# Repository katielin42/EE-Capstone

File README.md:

# EE-Capstone
This repository is the master collection of technical files (excluding reports and posters) for ECE490/491 group 1 capstone - Formula SAE EVCU (electric vehicle control unit) project. Group members are enrolled in electrical engineering at the U of A. Our valuable consultant and helpers are staff and instructors of ECE 490/491 as well as Le Minh Dang, a computer engineering student, all of whom are from the University of Alberta as well. 

## Hardware
Below is a high level hardware block diagram describing our fabricated PCB. Detailed 3d-view of the PCB and schematic can be found under Hardware Design/EVCU Rev B/EVCU. 

Design created by: Thomas Osei-Bonsu Jr. and Katie Lin

## Software
Below is a high level software flowchart block diagram describing our software control flow. Detailed Documentation about code can be found below. We are using STM32Cube IDE to develop our code currently, so our configuration for our software has mostly been STM32Cube IDE presets.

Design created by: Katie Lin and Thomas Osei-Bonsu Jr.

**Libraries/modules/middlewares we used:** 

+ **FreeRTOS**: for scheduling tasks and other parallel programming functionalities

+ **FATFS**: for communications and r/w functions with the SD card

**Current code structure**:

```STM32_test.ioc```: Settings file for pin configurations, turning peripherials on/off with STM32Cube IDE...etc.

```main.c```: pin defines, generation of global tasks/mutexes/threads and starting the kernel. Also imports all the other functions and runs them. 

```SD_task.c && SD_task.h```: calls functions to perform r/w functions to and from sd card, as well as mount/dismount...etc. 

```ADC_task.c && ADC_task.h```: processes values going into ADC pins and saves them in an intermediate buffer for further logic/processing. 

```CAN_task.c && CAN_task.h```: processes operations relevant to STM32 BxCAN functionalities, such as sending and receiving CAN messages, encoding and decoding of such messages...etc. 

```controller_task.c && controller_task.h```: a giant state machine with cases, interrupts...etc that links all the tasks together. Based on the inputs and outputs of the task files described above, decide the next steps of what the MCU needs to do, usually sending CAN messages and error logging upon error detection. 

## User Manual (for EVCU PCB)

Above is a physical image of the EVCU PCB. 

**Hardware Setup**

The setup for EVCU PCB should be done after reviewing the schematic and layout, which can be found under Hardware Design/EVCU Rev B/EVCU. For the EVCU PCB, provide a 12v DC input at J2 and ground signal. 

At J3, the APPS VPA/VPA2 and BSE sensor signal inputs to the ADC are labelled. Please consult the accelerator pedal datasheets to hook the APPS pedal/BSE sensors up correctly. 

The J5 DB9 connector is the CAN connector that can be hooked up to the motor controller. Our CAN bus speed is 0.5Mbit/second, so configure the motor controller accordingly. 

Before powering the board up, please ensure a microSD card is inserted and the sensors are powered and operational and connected to the analog inputs of this PCB. The current firmware will start running once the board is powered up. If any firmware errors occur, disconnect the PCB from power, ensure the hardware components are all connected, and reconnect the PCB to power. 

**Firmware Setup**

If one wishes to modify the firmware, please download STM32CubeIDE and clone this repository. The firmware project name in this repository is STM32_Test. Then, hook up serial wire debug pins in J1 to a debug programmer. These configurations can be found online. Then, clicking on the run or debug button will flash the updated code onto the EVCU PCB MCU. 

+ If the error conditions for the analog APPS/BSE sensors need to be modified, they can be changed in controller_task.c under the function check_error_condition(). Currently the code checks for APPS/BSE <0.5 or >4.5V as specified by the rules, but I believe the datasheet for one of the sensors says otherwise. 
+ If any CAN address/settings need to be modified, they can be changed in CAN_task.c

**Caveats**
+ If SD card logs aren't removed after powering off the board, they will be wiped at the next instance the board is powered up. 
+ SD card cannot be removed in the middle of operation. 
+ SD card might die due to too many writes, just replace a new micro SD card if you notice the EVCU firmware behaving weirdly with the SD card. 

**The code also works with the dev board. However, several changes need to be made in the .ioc**
+ uSD_detect pin needs to be changed from PC7 to PA5. 
+ Clock configurations need to be set: HSE from BYPASS to crystal/ceramic oscillator, and disable LSE. 
+ Connect the CAN transciever module to the dev board via the USB breakout board, connect to the non ST-Link microUSB input on the dev board (there are only two). 

Finally, save those changes to the .ioc file, close it, and flash the code onto the dev board.

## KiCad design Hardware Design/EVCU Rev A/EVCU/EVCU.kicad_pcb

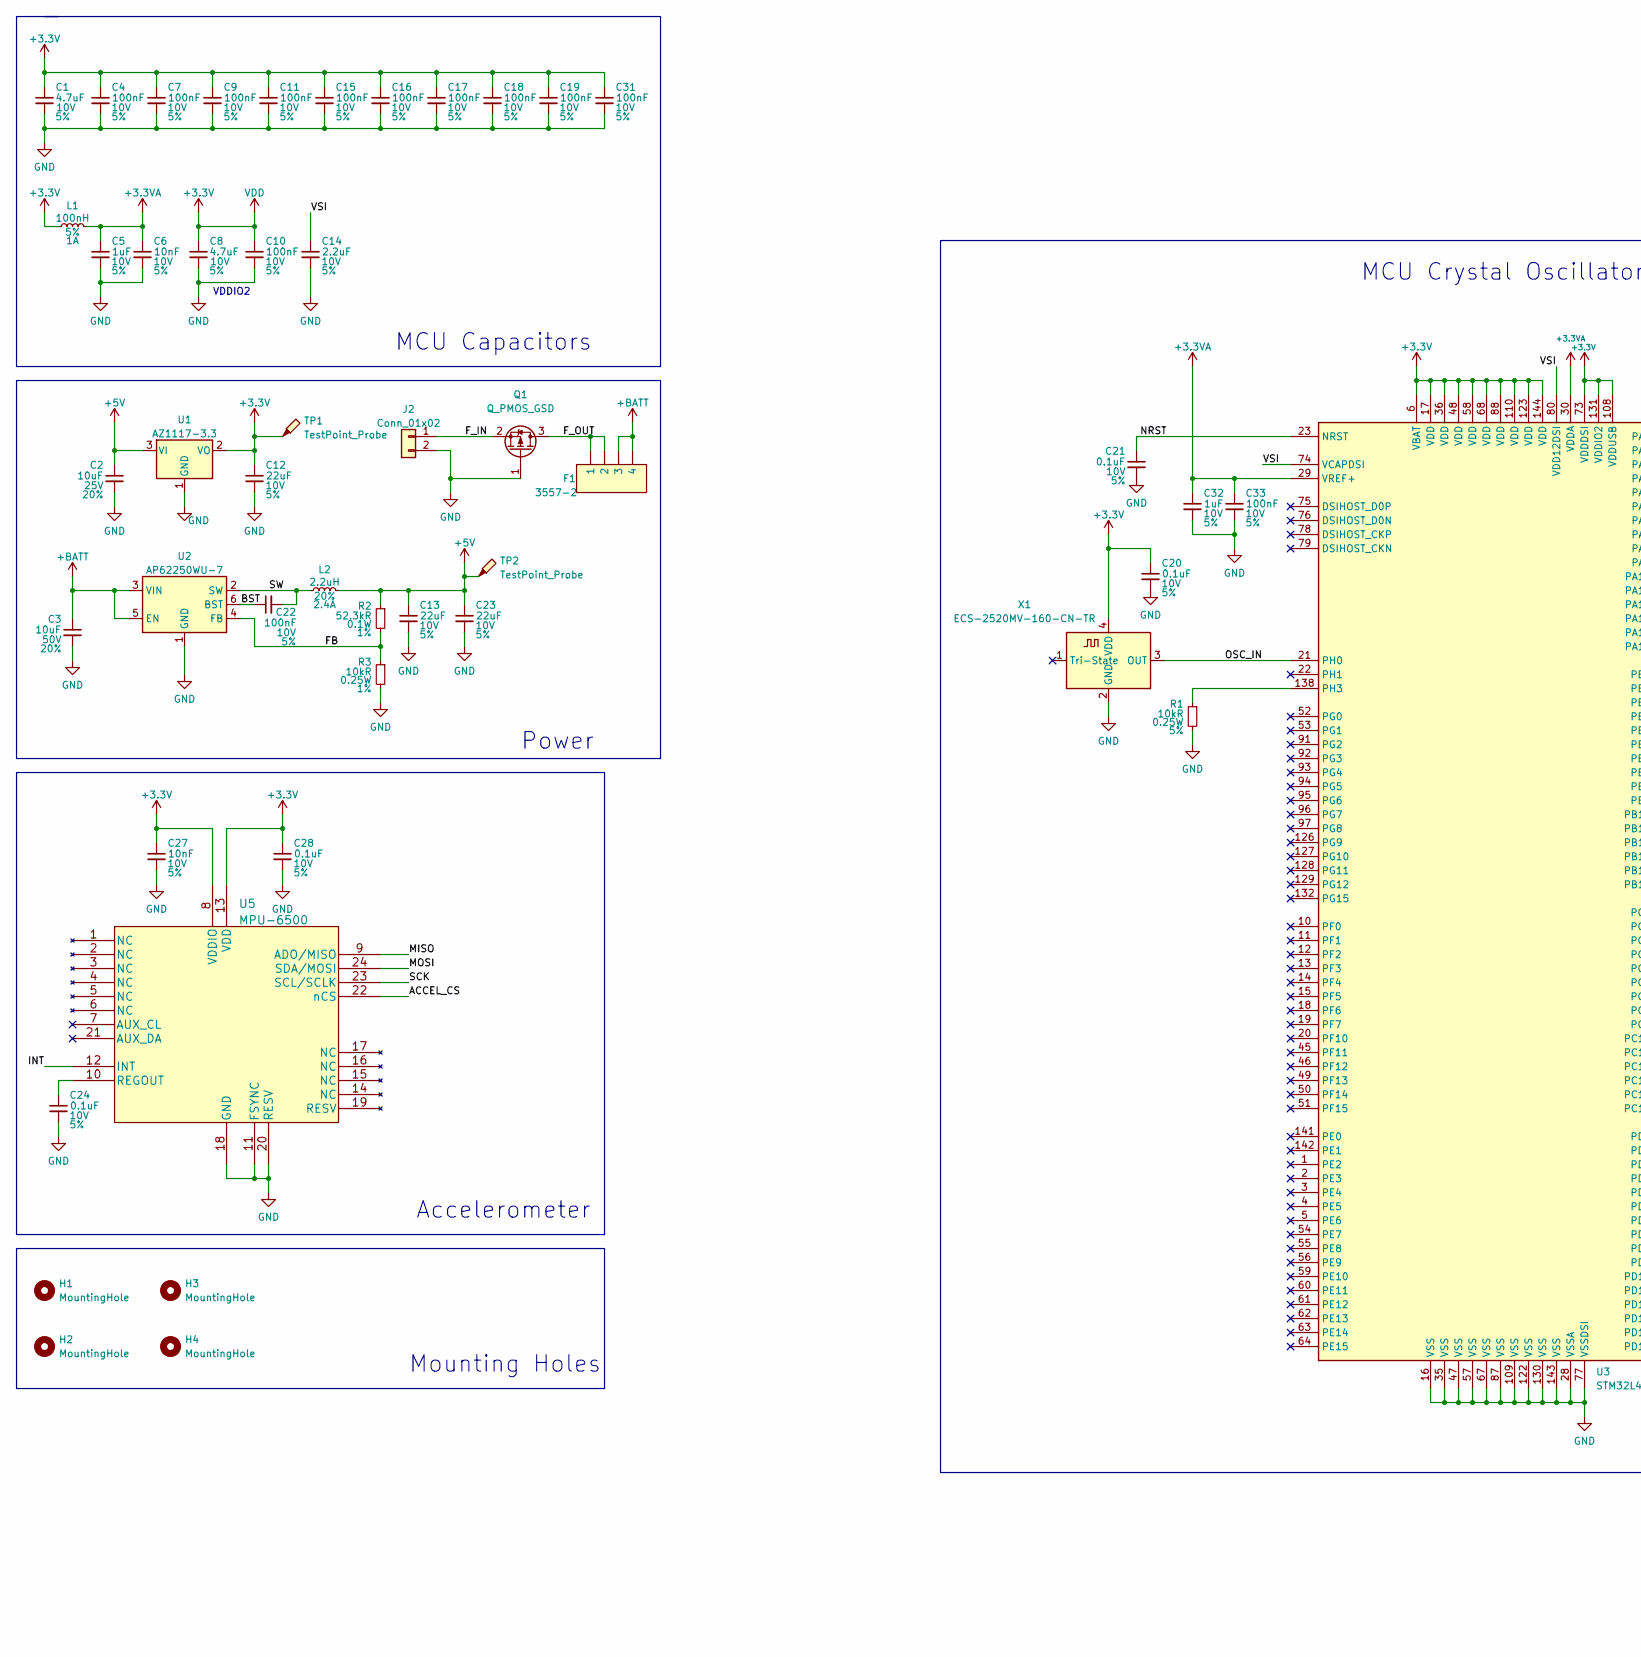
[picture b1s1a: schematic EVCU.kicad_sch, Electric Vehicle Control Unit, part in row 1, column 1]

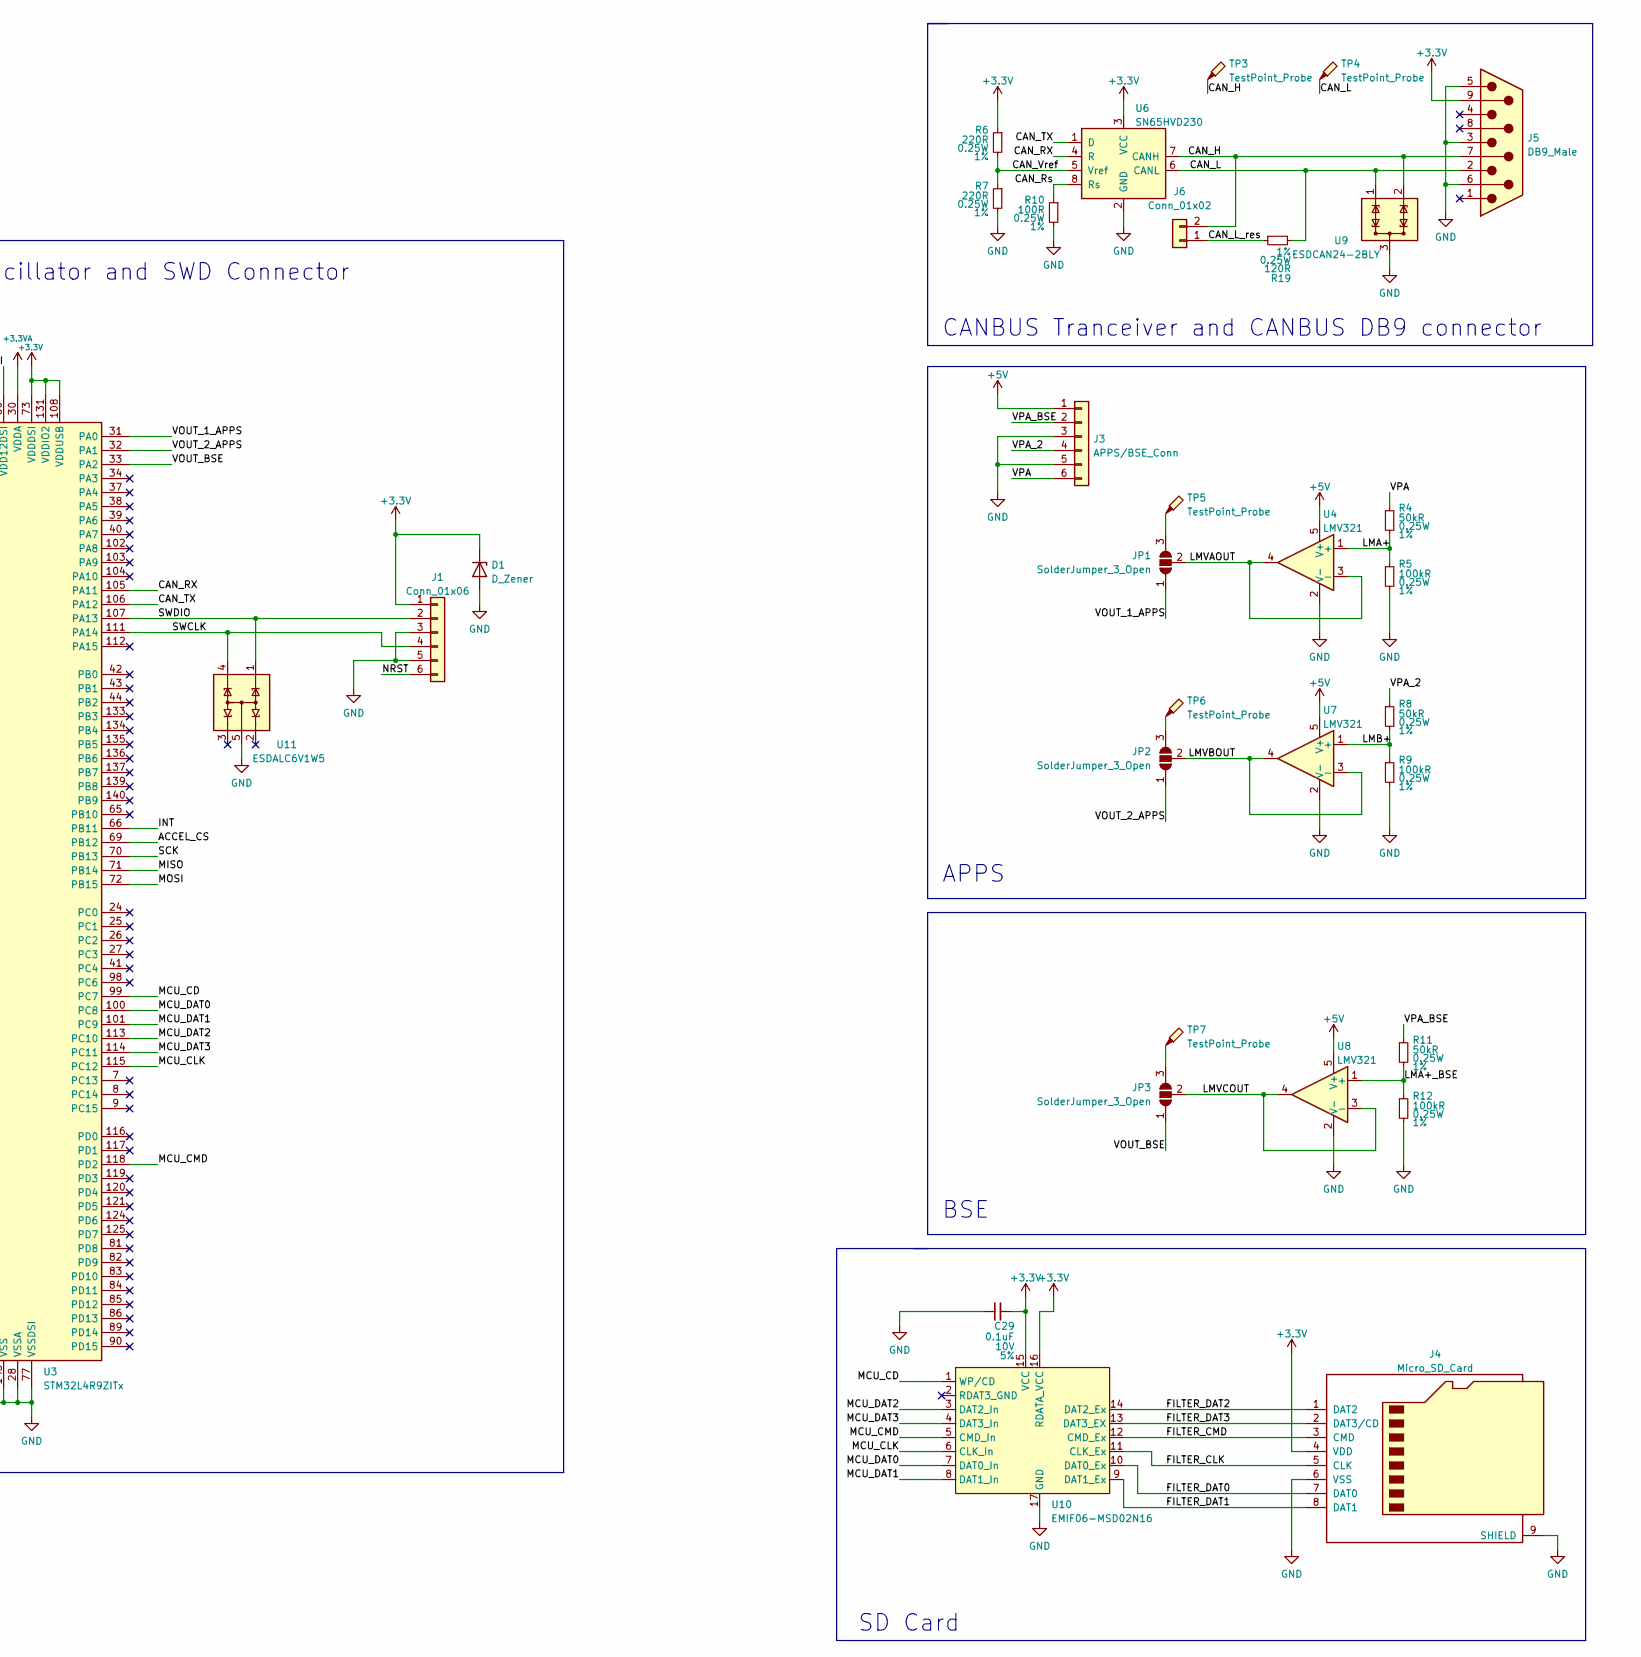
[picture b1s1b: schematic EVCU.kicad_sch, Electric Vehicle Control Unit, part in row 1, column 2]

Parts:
C1, C8: 4.7uF; C_0603_1608Metric_Pad1.08x0.95mm_HandSolder; Tolerance 5%; Rating 10V
C2: 10uF; C_0603_1608Metric_Pad1.08x0.95mm_HandSolder; Rating 25V; Tolerance 20%
C3: 10uF; C_1206_3216Metric_Pad1.33x1.80mm_HandSolder; Rating 50V; Tolerance 20%
C4, C7, C9, C10, C11, C15, C16, C17, C18, C19, C22, C31, C33: 100nF; C_0603_1608Metric_Pad1.08x0.95mm_HandSolder; Rating 10V; Tolerance 5%
C5, C32: 1uF; C_0603_1608Metric_Pad1.08x0.95mm_HandSolder; Rating 10V; Tolerance 5%
C6, C27: 10nF; C_0603_1608Metric_Pad1.08x0.95mm_HandSolder; Rating 10V; Tolerance 5%
C12, C13, C23: 22uF; C_0603_1608Metric_Pad1.08x0.95mm_HandSolder; Rating 10V; Tolerance 5%
C14: 2.2uF; C_0603_1608Metric_Pad1.08x0.95mm_HandSolder; Rating 10V; Tolerance 5%
C20, C21, C24, C28, C29: 0.1uF; C_0603_1608Metric_Pad1.08x0.95mm_HandSolder; Rating 10V; Tolerance 5%
D1: D_Zener; D_SMB
F1: 3557-2
H1, H2, H3, H4: MountingHole; MountingHole_2.2mm_M2_DIN965_Pad
J1: Conn_01x06; PinSocket_1x06_P2.54mm_Vertical
J2: Conn_01x02; TerminalBlock_Phoenix_PT-1,5-2-3.5-H_1x02_P3.50mm_Horizontal
J3: APPS/BSE_Conn; TerminalBlock_Phoenix_PT-1,5-6-3.5-H_1x06_P3.50mm_Horizontal
J4: Micro_SD_Card; microSD_HC_Wuerth_693072010801
J5: DB9_Male; DSUB-9_Male_Horizontal_P2.77x2.84mm_EdgePinOffset7.70mm_Hou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
J6: Conn_01x02; PinHeader_1x02_P2.54mm_Vertical
JP1, JP2, JP3: SolderJumper_3_Open; SolderJumper-3_P1.3mm_Open_Pad1.0x1.5mm_NumberLabels
L1: 100nH; L_1210_3225Metric_Pad1.42x2.65mm_HandSolder; Rating 1A; Tolerance 5%
L2: 2.2uH; L_1008_2520Metric_Pad1.43x2.20mm_HandSolder; Rating 2.4A; Tolerance 20%
Q1: Q_PMOS_GSD; SOT-23
R1: 10kR; R_0805_2012Metric_Pad1.20x1.40mm_HandSolder; Rating 0.25W; Tolerance 5%
R2: 52.3kR; R_0805_2012Metric_Pad1.20x1.40mm_HandSolder; Rating 0.1W; Tolerance 1%
R3: 10kR; R_0805_2012Metric_Pad1.20x1.40mm_HandSolder; Rating 0.25W; Tolerance 1%
R4, R8, R11: 50kR; R_0805_2012Metric_Pad1.20x1.40mm_HandSolder; Rating 0.25W; Tolerance 1%
R5, R9, R12: 100kR; R_0805_2012Metric_Pad1.20x1.40mm_HandSolder; Rating 0.25W; Tolerance 1%
R6, R7: 220R; R_0805_2012Metric_Pad1.20x1.40mm_HandSolder; Rating 0.25W; Tolerance 1%
R10: 100R; R_0805_2012Metric_Pad1.20x1.40mm_HandSolder; Rating 0.25W; Tolerance 1%
R19: 120R; R_0805_2012Metric_Pad1.20x1.40mm_HandSolder; Rating 0.25W; Tolerance 1%
TP1, TP2, TP3, TP4, TP5, TP6, TP7: TestPoint_Probe; TestPoint_Pad_1.5x1.5mm
U1: AZ1117-3.3; SOT-89-3_Handsoldering
U2: AP62250WU-7; TSOT-23-6_HandSoldering
U3: STM32L4R9ZITx; LQFP-144_20x20mm_P0.5mm
U4, U7, U8: LMV321; SOT-353_SC-70-5_Handsoldering
U5: MPU-6500; QFN-24_3x3mm_P0.4mm
U6: SN65HVD230; SOIC-8_3.9x4.9mm_P1.27mm
U9: ESDCAN24-2BLY; SC-59
U10: EMIF06-MSD02N16
U11: ESDALC6V1W5; SOT-353_SC-70-5_Handsoldering
X1: ECS-2520MV-160-CN-TR; Oscillator_SMD_ECS_2520MV-xxx-xx-4Pin_2.5x2.0mm

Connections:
+3.3VA: C5.1, C6.1, C32.1, C33.1, L1.2, U3.29 (VREF+), U3.30 (VDDA)
+3V3: C1.1, C4.1, C7.1, C8.1, C9.1, C10.1, C11.1, C12.1, C15.1, C16.1, C17.1, C18.1, C19.1, C20.1, C27.1, C28.1, C29.2, C31.1, D1.1 (K), J1.1, J4.4 (VDD), J5.9, L1.1, R6.1, TP1.1, U1.2 (VO), U3.6 (VBAT), U3.17 (VDD), U3.36 (VDD), U3.48 (VDD), U3.58 (VDD), U3.68 (VDD), U3.73 (VDDDSI), U3.88 (VDD), U3.108 (VDDUSB), U3.110 (VDD), U3.123 (VDD), U3.131 (VDDIO2), U3.144 (VDD), U5.8 (VDDIO), U5.13 (VDD), U6.3 (VCC), U10.15 (VCC), U10.16 (RDATA_VCC), X1.4 (VDD)
+5V: C2.1, C13.1, C23.1, J3.1, L2.2, R2.1, TP2.1, U1.3 (VI), U4.5 (V+), U7.5 (V+), U8.5 (V+)
+BATT: C3.1, F1., F1.3, F1.4, U2.3 (VIN), U2.5 (EN)
/ACCEL_CS: U3.69 (PB12), U5.22 (nCS)
/BST: C22.1, U2.6 (BST)
/CAN_H: J5.7, J6.2, TP3.1, U6.7 (CANH), U9.2
/CAN_L: J5.2, R19.2, TP4.1, U6.6 (CANL), U9.1
/CAN_L_res: J6.1, R19.1
/CAN_RX: U3.105 (PA11), U6.4 (R)
/CAN_Rs: R10.1, U6.8 (Rs)
/CAN_TX: U3.106 (PA12), U6.1 (D)
/CAN_Vref: R6.2, R7.1, U6.5 (Vref)
/FB: R2.2, R3.1, U2.4 (FB)
/FILTER_CLK: J4.5 (CLK), U10.11 (CLK_Ex)
/FILTER_CMD: J4.3 (CMD), U10.12 (CMD_Ex)
/FILTER_DAT0: J4.7 (DAT0), U10.10 (DAT0_Ex)
/FILTER_DAT1: J4.8 (DAT1), U10.9 (DAT1_Ex)
/FILTER_DAT2: J4.1 (DAT2), U10.14 (DAT2_Ex)
/FILTER_DAT3: J4.2 (DAT3/CD), U10.13 (DAT3_EX)
/F_IN: J2.1, Q1.2 (S)
/F_OUT: F1., F1.1, F1.2, Q1.3 (D)
/INT: U3.66 (PB11), U5.12 (INT)
/LMA+: R4.2, R5.1, U4.1 (+)
/LMA+_BSE: R11.2, R12.1, U8.1 (+)
/LMB+: R8.2, R9.1, U7.1 (+)
/LMVAOUT: JP1.2 (C), U4.3 (-), U4.4
/LMVBOUT: JP2.2 (C), U7.3 (-), U7.4
/LMVCOUT: JP3.2 (C), U8.3 (-), U8.4
/MCU_CD: U3.99 (PC7), U10.1 (WP/CD)
/MCU_CLK: U3.115 (PC12), U10.6 (CLK_In)
/MCU_CMD: U3.118 (PD2), U10.5 (CMD_In)
/MCU_DAT0: U3.100 (PC8), U10.7 (DAT0_In)
/MCU_DAT1: U3.101 (PC9), U10.8 (DAT1_In)
/MCU_DAT2: U3.113 (PC10), U10.3 (DAT2_In)
/MCU_DAT3: U3.114 (PC11), U10.4 (DAT3_In)
/MISO: U3.71 (PB14), U5.9 (ADO/MISO)
/MOSI: U3.72 (PB15), U5.24 (SDA/MOSI)
/NRST: C21.1, J1.6, U3.23 (NRST)
/OSC_IN: U3.21 (PH0), X1.3 (OUT)
/SCK: U3.70 (PB13), U5.23 (SCL/SCLK)
/SW: C22.2, L2.1, U2.2 (SW)
/SWCLK: J1.4, U3.111 (PA14), U11.4
/SWDIO: J1.2, U3.107 (PA13), U11.1
/VOUT_1_APPS: JP1.1 (A), U3.31 (PA0)
/VOUT_2_APPS: JP2.1 (A), U3.32 (PA1)
/VOUT_BSE: JP3.1 (A), U3.33 (PA2)
/VPA: J3.6, R4.1
/VPA_2: J3.4, R8.1
/VPA_BSE: J3.2, R11.1
/VSI: C14.1, U3.74 (VCAPDSI), U3.80 (VDD12DSI)
GND: C1.2, C2.2, C3.2, C4.2, C5.2, C6.2, C7.2, C8.2, C9.2, C10.2, C11.2, C12.2, C13.2, C14.2, C15.2, C16.2, C17.2, C18.2, C19.2, C20.2, C21.2, C23.2, C24.2, C27.2, C28.2, C29.1, C31.2, C32.2, C33.2, D1.2 (A), H1.1, H2.1, H3.1, H4.1, J1.3, J1.5, J2.2, J3.3, J3.5, J4.6 (VSS), J4.9 (SHIELD), J5.0, J5.3, J5.5, J5.6, Q1.1 (G), R1.2, R3.2, R5.2, R7.2, R9.2, R10.2, R12.2, U1.1 (GND), U2.1 (GND), U3.16 (VSS), U3.28 (VSSA), U3.35 (VSS), U3.47 (VSS), U3.57 (VSS), U3.67 (VSS), U3.77 (VSSDSI), U3.87 (VSS), U3.109 (VSS), U3.122 (VSS), U3.130 (VSS), U3.143 (VSS), U4.2 (V-), U5.11 (FSYNC), U5.18 (GND), U5.20 (RESV), U6.2 (GND), U7.2 (V-), U8.2 (V-), U9.3, U10.17 (GND), U11.5, X1.2 (GND)
unnamed: C24.1, U5.10 (REGOUT)
unnamed: JP1.3 (B), TP5.1
unnamed: JP2.3 (B), TP6.1
unnamed: JP3.3 (B), TP7.1
unnamed: R1.1, U3.138 (PH3)

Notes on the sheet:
Accelerometer
SD Card
Power
BSE
MCU Capacitors
VDDIO2
CANBUS Tranceiver and CANBUS DB9 connector
APPS
MCU Crystal Oscillator and SWD Connector
Mounting Holes

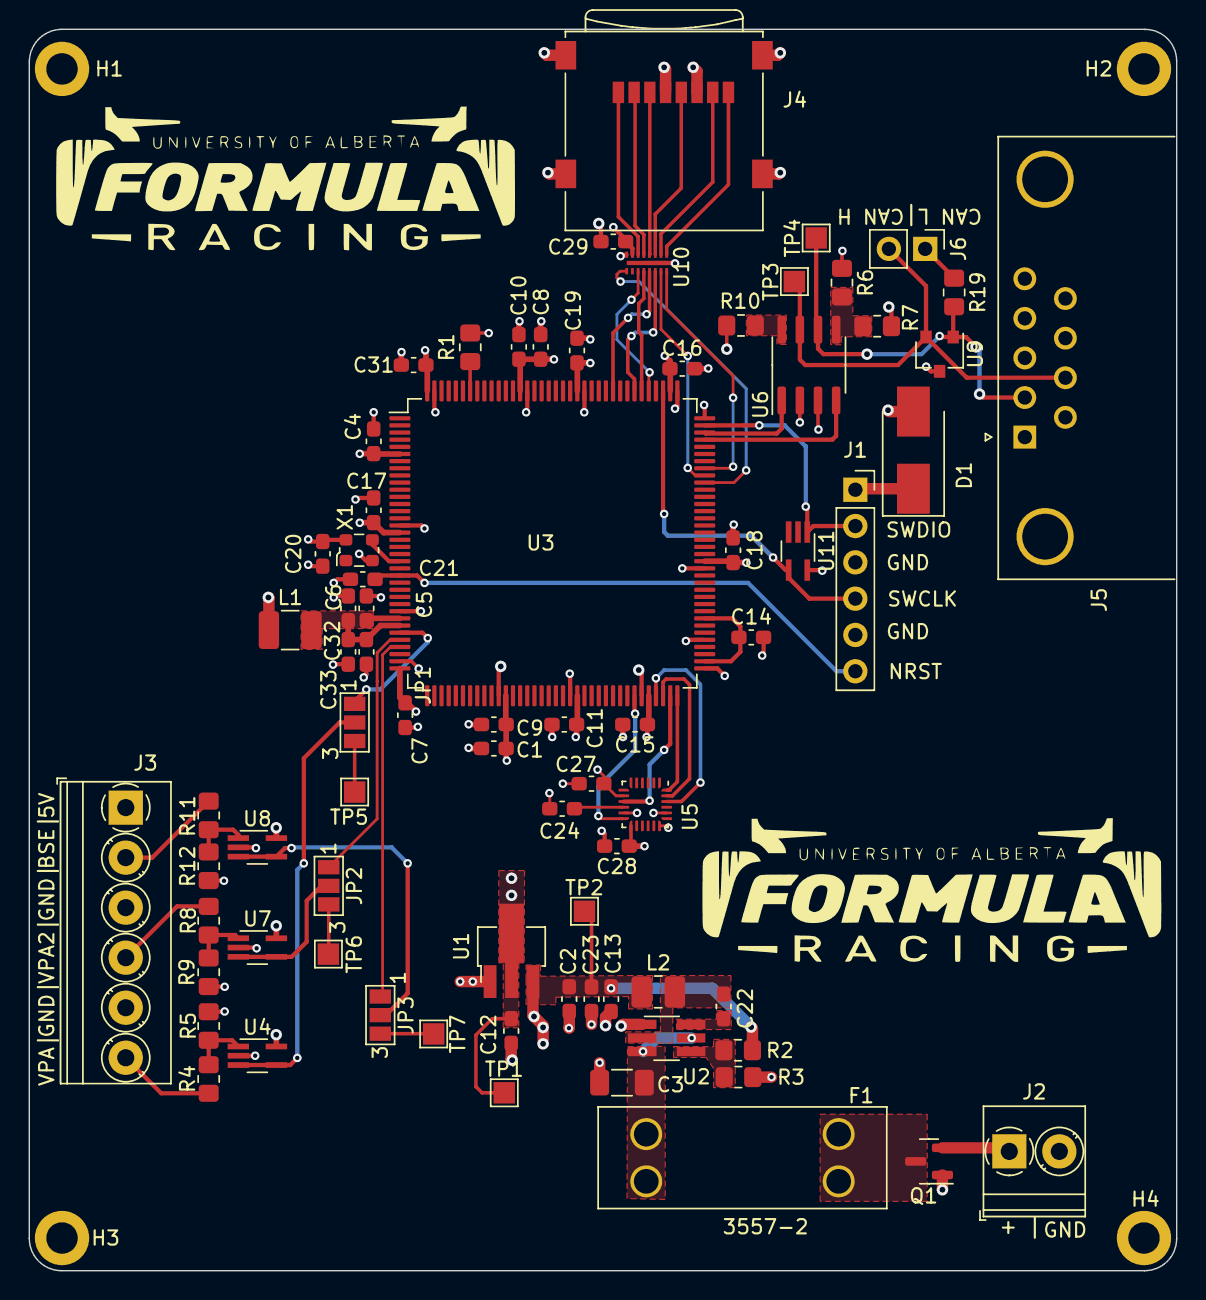
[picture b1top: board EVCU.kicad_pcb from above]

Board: 4 copper layers, 80.3 x 86.8 mm, 80 parts (0 on the bottom side), 57 nets.

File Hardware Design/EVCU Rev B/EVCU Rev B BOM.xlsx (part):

Name | PCB Annotation | Value | Manufacturer | Mfr. P/N | Quantity | Description | Supplier | Supplier Link | Component Cost | Component Cost
STM32L4R9ZIT6 | U3 | IC MCU 32BIT 2MB FLASH 144LQFP | STMicroelectronics | STM32L4R9ZIT6 | 1 | ARM® Cortex®-M4 STM32L4R Microcontroller IC 32-Bit Single-Core 120MHz 2MB (2M x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 | Digikey | https://www.digikey.ca/en/products/detail/stmicroelectronics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 | 35.44 | 118.61
AZ1117CR-3.3TRG1 | U1 | IC REG LINEAR 3.3V 1A SOT89 | Diodes Incorporated | AZ1117CR-3.3TRG1 | 1 | Linear Voltage Regulator IC Positive Fixed 1 Output 1A SOT-89-3 | Digikey | https://www.digikey.ca/en/products/detail/diodes-incorporate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 | 0.69
AP62250WU-7 | U2 | DCDC CONV HV BUCK TSOT26 T&R 3K | Diodes Incorporated | AP62250WU-7 | 1 | Buck Switching Regulator IC Positive Adjustable 0.8V 1 Output 2.5A SOT-23-6 Thi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 | Digikey | https://www.digikey.ca/en/products/detail/diodes-incorporate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 | 0.77
ECS-2520MV-160-CN-TR | X1 | OSC XO 16.000MHZ CMOS SMD | ECS Inc. | ECS-2520MV-160-CN-TR | 1 | 16 MHz XO (Standard) HCMOS Oscillator 1.6V ~ 3.6V Enable/Disable 4-SMD, No Lead | Digikey | https://www.digikey.ca/en/products/detail/ecs-inc/ECS-2520MV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 | 1.87
MPU-6500 | U5 | IMU ACCEL/GYRO 3-AXIS I2C 24QFN | TDK InvenSense | MPU-6500 | 1 | Accelerometer, Gyroscope, 6 Axis Sensor I²C, SPI Output | Digikey | https://www.digikey.ca/en/products/detail/tdk-invensense/MPU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 | 14.28
SN65HVD230QD | U6 | IC TRANSCEIVER HALF 1/1 8SOIC | Texas Instruments | SN65HVD230QDR | 1 | 1/1 Transceiver Half CANbus 8-SOIC | Digikey | https://www.digikey.ca/en/products/detail/texas-instruments/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 | 4.79
LMV321WG-7 | U4, U7, U8 | IC OPAMP GP 1 CIRCUIT SOT25 | Diodes Incorporated | LMV321WG-7 | 3 | General Purpose Amplifier 1 Circuit Rail-to-Rail SOT-25 | Digikey | https://www.digikey.ca/en/products/detail/diodes-incorporate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 | 6.41
ESDCAN24-2BLY | U9 | TVS DIODE 24VWM 40VC SOT23-3 | STMicroelectronics | ESDCAN24-2BLY | 1 | 40V Clamp 5.5A (8/20µs) Ipp Tvs Diode Surface Mount SOT-23-3 | Digikey | https://www.digikey.ca/en/products/detail/stmicroelectronics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 | 0.71
EMIF06-MSD02N16 | U10 | FILTER RC(PI) 45 OHM/20PF SMD | STMicroelectronics | EMIF06-MSD02N16 | 1 | RC (Pi) EMI Filter 2nd Order Low Pass 6 Channel R = 45Ohms, C = 20pF (Total) 16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 | Digikey | https://www.digikey.ca/en/products/detail/stmicroelectronics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 | 1.76
ESDALC6V1W5 | U11 | TVS DIODE 3VWM SOT323-5 | STMicroelectronics | ESDALC6V1W5 | 1 | Clamp Ipp Tvs Diode Surface Mount SOT-323-5 | Digikey | https://www.digikey.ca/en/products/detail/stmicroelectronics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 | 0.79
PJA3405_R1_00001 | Q1 | SOT-23, MOSFET | Panjit International Inc. | PJA3405_R1_00001 | 1 | P-Channel 30 V 3.6A (Ta) 1.25W (Ta) Surface Mount SOT-23 | Digikey | https://www.digikey.ca/en/products/detail/panjit-internation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 | 0.71
0287001.PXCN | F1 | FUSE AUTO 1A 32VDC BLADE | Littelfuse Inc. | 0287001.PXCN | 1 | 1 A AC 32 V DC Fuse Automotive Requires Holder Blade, ATO/ATC | Digikey | https://www.digikey.ca/en/products/detail/littelfuse-inc/028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 | 0.48
3557_02 | F1 | FUSE BLOCK BLADE 500V 30A PCB | Keystone Electronics | 3557_02 | 1 | Fuse Block 30 A 500V 1 Circuit Blade Through Hole | Digikey | https://www.digikey.ca/en/products/detail/keystone-electroni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 | 2.09
SMBJ3V3-E3/5B | D1 | TVS DIODE 3.3VWM 10.3VC DO214AA | Vishay General Semiconductor - Diodes Division | SMBJ3V3-E3/5B | 1 | 10.3V Clamp 200A (8/20µs) Ipp Tvs Diode Surface Mount DO-214AA (SMBJ) | Digikey | https://www.digikey.ca/en/products/detail/vishay-general-sem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 | 0.76
VJ0603Y104JXQPW1BC | C4, C7, C9, C10, C11, C15, C16, C17, C18, C19, C22, C31, C33, C20, C24, C25, C2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 | CAP CER 0.1UF 10V X7R 0603 | Vishay Vitramon | VJ0603Y104JXQPW1BC | 21 | 0.1 µF ±5% 10V Ceramic Capacitor X7R 0603 (1608 Metric) | Digikey | https://www.digikey.ca/en/products/detail/vishay-vitramon/VJ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 | 5.48
CL10A475KP8NNNC | C1, C8 | CAP CER 4.7UF 10V X5R 0603 | Samsung Electro-Mechanics | CL10A475KP8NNNC | 2 | 4.7 µF ±10% 10V Ceramic Capacitor X5R 0603 (1608 Metric) | Digikey | https://www.digikey.ca/en/products/detail/samsung-electro-me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 | 1.7
CL31A106MBHNNNE | C3 | CAP CER 10UF 50V X5R 1206 | Samsung Electro-Mechanics | CL31A106MBHNNNE | 1 | 10 µF ±20% 50V Ceramic Capacitor X5R 1206 (3216 Metric) | Digikey | https://www.digikey.ca/en/products/detail/samsung-electro-me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 | 2.69
CL10A106MA8NRNC | C2 | 10 µF ±20% 25V Ceramic Capacitor X5R 0603 (1608 Metric) | Samsung Electro-Mechanics | CL10A106MA8NRNC | 1 | 10 µF ±20% 25V Ceramic Capacitor X5R 0603 (1608 Metric) | Digikey | https://www.digikey.ca/en/products/detail/samsung-electro-me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 | 2.58
CL10B105KP8NNNC | C5, C32 | CAP CER 1UF 10V X7R 0603 | Samsung Electro-Mechanics | CL10B105KP8NNNC | 2 | 1 µF ±10% 10V Ceramic Capacitor X7R 0603 (1608 Metric) | Digikey | https://www.digikey.ca/en/products/detail/samsung-electro-me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 | 0.55000000000000004
C1608X5R1A226M080AC | C13, C23, C12 | CAP CER 22UF 10V X5R 0603 | TDK Corporation | C1608X5R1A226M080AC | 3 | 22 µF ±20% 10V Ceramic Capacitor X5R 0603 (1608 Metric) | Digikey | https://www.digikey.ca/en/products/detail/tdk-corporation/C1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 | 4.51
GRM188R71A225KE15D | C14 | CAP CER 2.2UF 10V X7R 0603 | Murata Electronics | GRM188R71A225KE15D | 1 | 2.2 µF ±10% 10V Ceramic Capacitor X7R 0603 (1608 Metric) | Digikey | https://www.digikey.ca/en/products/detail/murata-electronics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 | 1.41
885012206014 | C6, C27 | CAP CER 10000PF 10V X7R 0603 | Würth Elektronik | 885012206014 | 2 | 10000 pF ±10% 10V Ceramic Capacitor X7R 0603 (1608 Metric) | Digikey | https://www.digikey.ca/en/products/detail/w%C3%BCrth-elektro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 | 0.33
36502C39NJTDG | L1 | FIXED IND 100NH 8A 8 MOHM SMD | TDK Corporation | TFM322512ALMAR10MTAA | 1 | 100 nH Unshielded Thin Film Inductor 8 A 8mOhm Max 1210 (3225 Metric) | Digikey | https://www.digikey.ca/en/products/detail/tdk-corporation/TF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 | 2.98
CIGT252010EH2R2MNE | L2 | FIXED IND 2.2UH 2.4A 80MOHM SMD | Samsung Electro-Mechanics | CIGT252010EH2R2MNE | 1 | 2.2 µH Unshielded Thin Film Inductor 2.4 A 80mOhm Max 1008 (2520 Metric) | Digikey | https://www.digikey.ca/en/products/detail/samsung-electro-me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 | 0.8
RNCP0805FTD10K0 | R1, R3 | RES 10K OHM 1% 1/4W 0805 | Stackpole Electronics Inc | RNCP0805FTD10K0 | 2 | 10 kOhms ±1% 0.25W, 1/4W Chip Resistor 0805 (2012 Metric) Anti-Sulfur Thin Film | Digikey | https://www.digikey.ca/en/products/detail/stackpole-electron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 | 1.1200000000000001
ERJ-6ENF5232V | R2 | RES SMD 52.3K OHM 1% 1/8W 0805 | Panasonic Electronic Components | ERJ-6ENF5232V | 1 | 52.3 kOhms ±1% 0.125W, 1/8W Chip Resistor 0805 (2012 Metric) Automotive AEC-Q20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 | Digikey | https://www.digikey.ca/en/products/detail/panasonic-electron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 | 1.41
RK73H2ATTD2200F | R6, R7 | RES 220 OHM 1% 1/4W 0805 | KOA Speer Electronics, Inc. | RK73H2ATTD2200F | 2 | 220 Ohms ±1% 0.25W, 1/4W Chip Resistor 0805 (2012 Metric) Automotive AEC-Q200, 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 | Digikey | https://www.digikey.ca/en/products/detail/koa-speer-electron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 | 0.6
AC0805FR-7W100KL | R5, R9, R12 | RES 100 KOHM 1% 1/4W 0805 | YAGEO | AC0805FR-7W100KL | 9 | 100 kOhms ±1% 0.25W, 1/4W Chip Resistor 0805 (2012 Metric) Automotive AEC-Q200,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 | Digikey | https://www.digikey.ca/en/products/detail/yageo/AC0805FR-7W1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 | 1.1399999999999999
RNCP0805FTD100R | R10 | RES 100 OHM 1% 1/4W 0805 | Stackpole Electronics Inc | RNCP0805FTD100R | 1 | 100 Ohms ±1% 0.25W, 1/4W Chip Resistor 0805 (2012 Metric) Anti-Sulfur Thin Film | Digikey | https://www.digikey.ca/en/products/detail/stackpole-electron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 | 1.1200000000000001
RC0805JR-0751KL | R4, R11, R8 | RES 51K OHM 5% 1/8W 0805 | YAGEO | RC0805JR-0751KL | 3 | 51 kOhms ±5% 0.125W, 1/8W Chip Resistor 0805 (2012 Metric) Moisture Resistant T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 | Digikey | https://www.digikey.ca/en/products/detail/yageo/RC0805JR-075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 | 0.43
RK73B2ATTD121J | R19 | RES 120 OHM 5% 1/4W 0805 | KOA Speer Electronics, Inc. | RK73B2ATTD121J | 1 | 120 Ohms ±5% 0.25W, 1/4W Chip Resistor 0805 (2012 Metric) Automotive AEC-Q200 T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 | Digikey | https://www.digikey.ca/en/products/detail/koa-speer-electron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 | 0.49
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
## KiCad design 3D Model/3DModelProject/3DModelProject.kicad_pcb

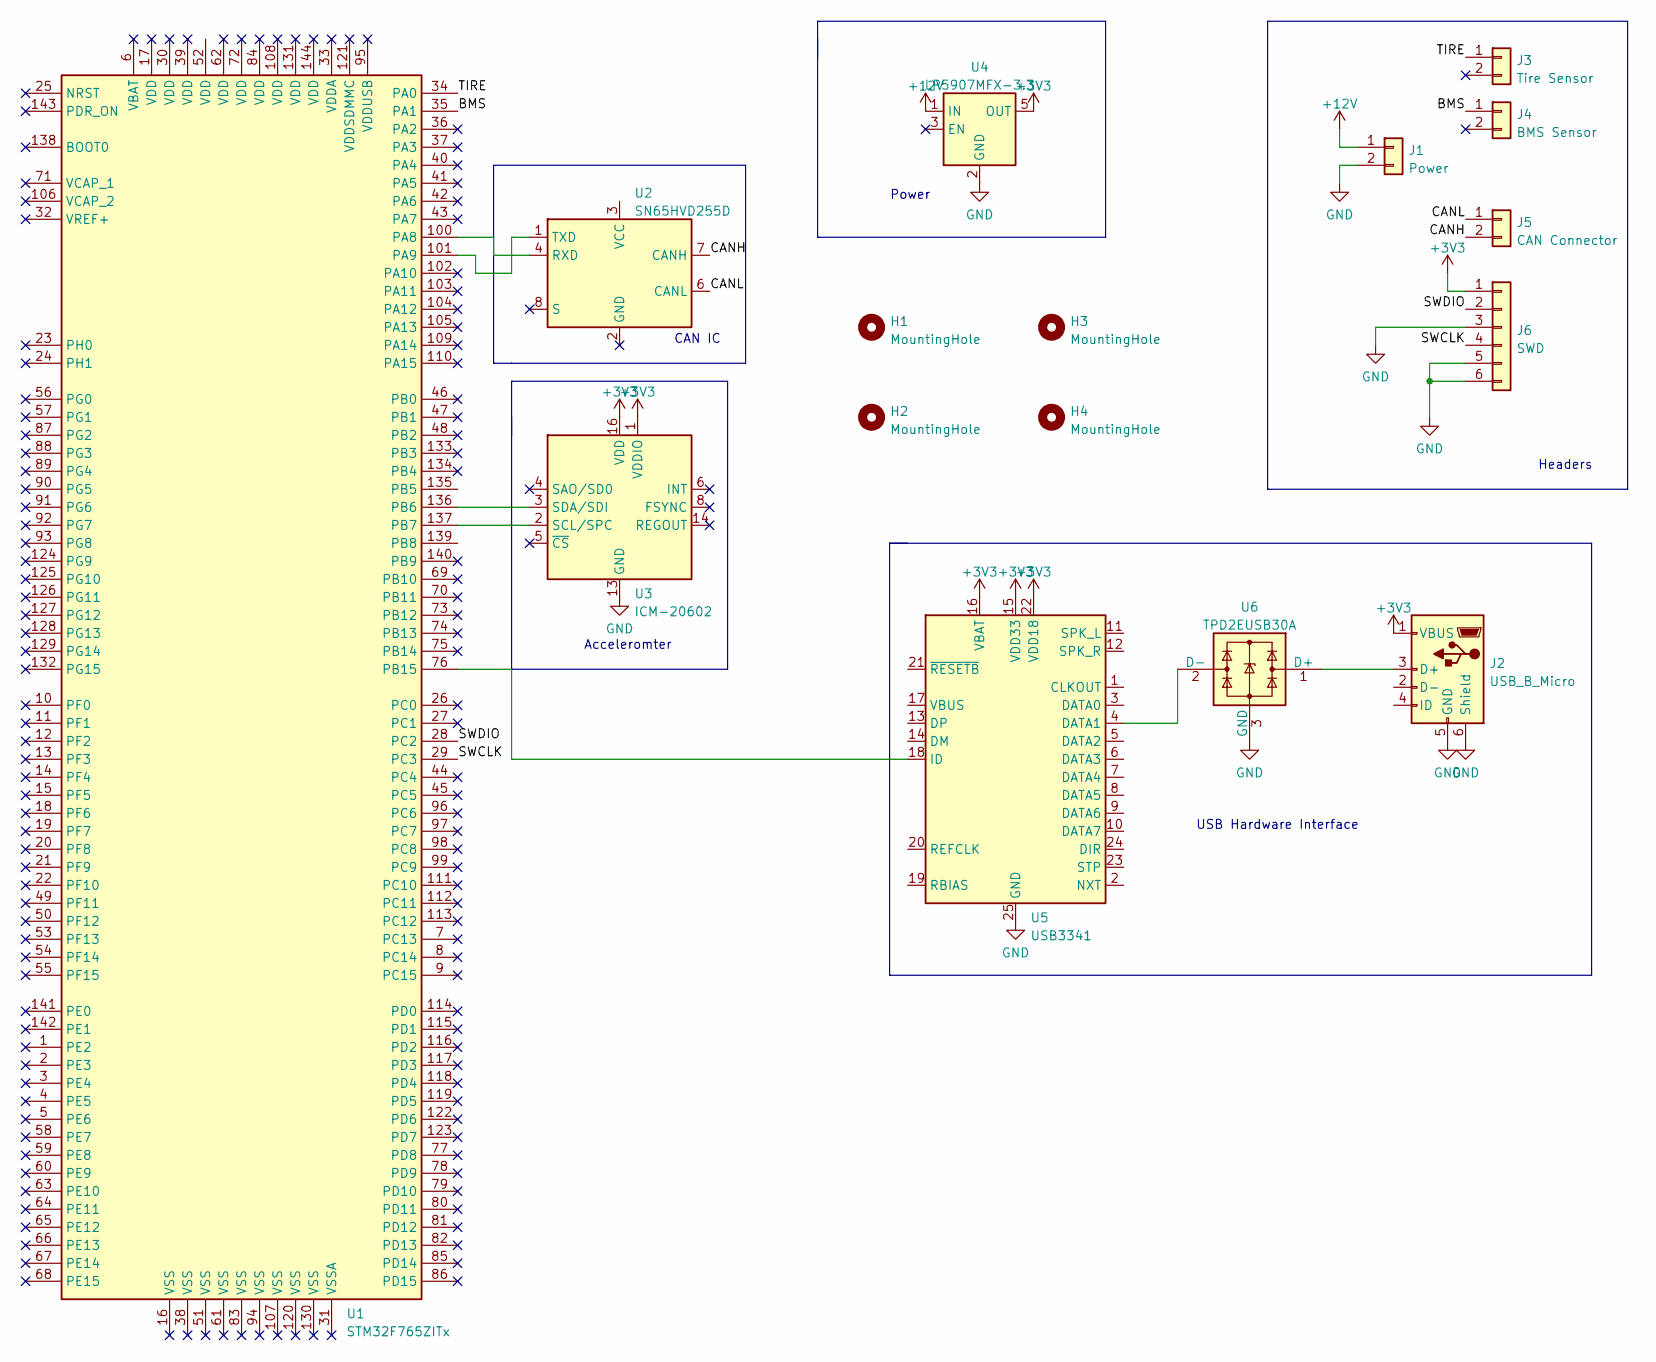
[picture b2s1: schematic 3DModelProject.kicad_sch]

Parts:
H1, H2, H3, H4: MountingHole; MountingHole_2.5mm_Pad_TopBottom
J1: Power; PhoenixContact_MC_1,5_2-G-3.5_1x02_P3.50mm_Horizontal
J2: USB_B_Micro; USB_Micro-B_Molex-105017-0001
J3: Tire Sensor; PhoenixContact_MC_1,5_2-G-3.5_1x02_P3.50mm_Horizontal
J4: BMS Sensor; PhoenixContact_MC_1,5_2-G-3.5_1x02_P3.50mm_Horizontal
J5: CAN Connector; PhoenixContact_MC_1,5_2-G-3.5_1x02_P3.50mm_Horizontal
J6: SWD; PinHeader_1x06_P2.54mm_Vertical
U1: STM32F765ZITx; LQFP-144_20x20mm_P0.5mm
U2: SN65HVD255D; SOIC-8_3.9x4.9mm_P1.27mm
U3: ICM-20602; LGA-16_3x3mm_P0.5mm_LayoutBorder3x5y
U4: LP5907MFX-3.3; SOT-23-5
U5: USB3341; QFN-24-1EP_4x4mm_P0.5mm_EP2.6x2.6mm
U6: TPD2EUSB30A; Texas_DRT-3

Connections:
+3V3: J2.1 (VBUS), J6.1, U3.1 (VDDIO), U3.16 (VDD), U4.5 (OUT), U5.15 (VDD33), U5.16 (VBAT), U5.22 (VDD18)
+12V: J1.1, U4.1 (IN)
/BMS: J4.1, U1.35 (PA1)
/CANH: J5.2, U2.7 (CANH)
/CANL: J5.1, U2.6 (CANL)
/SWCLK: J6.4, U1.29 (PC3)
/SWDIO: J6.2, U1.28 (PC2)
/TIRE: J3.1, U1.34 (PA0)
GND: J1.2, J2.5 (GND), J2.6 (Shield), J6.3, J6.5, J6.6, U3.9 (GND), U3.10 (GND), U3.11 (GND), U3.12 (GND), U3.13 (GND), U3.15 (GND), U4.2 (GND), U5.25 (GND), U6.3 (GND)
unnamed: J2.3 (D+), U6.1 (D+)
unnamed: U1.76 (PB15), U5.18 (ID)
unnamed: U1.100 (PA8), U2.4 (RXD)
unnamed: U1.101 (PA9), U2.1 (TXD)
unnamed: U1.136 (PB6), U3.3 (SDA/SDI)
unnamed: U1.137 (PB7), U3.2 (SCL/SPC)
unnamed: U5.4 (DATA1), U6.2 (D-)

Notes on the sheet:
CAN IC
USB Hardware Interface
Headers
Acceleromter
Power

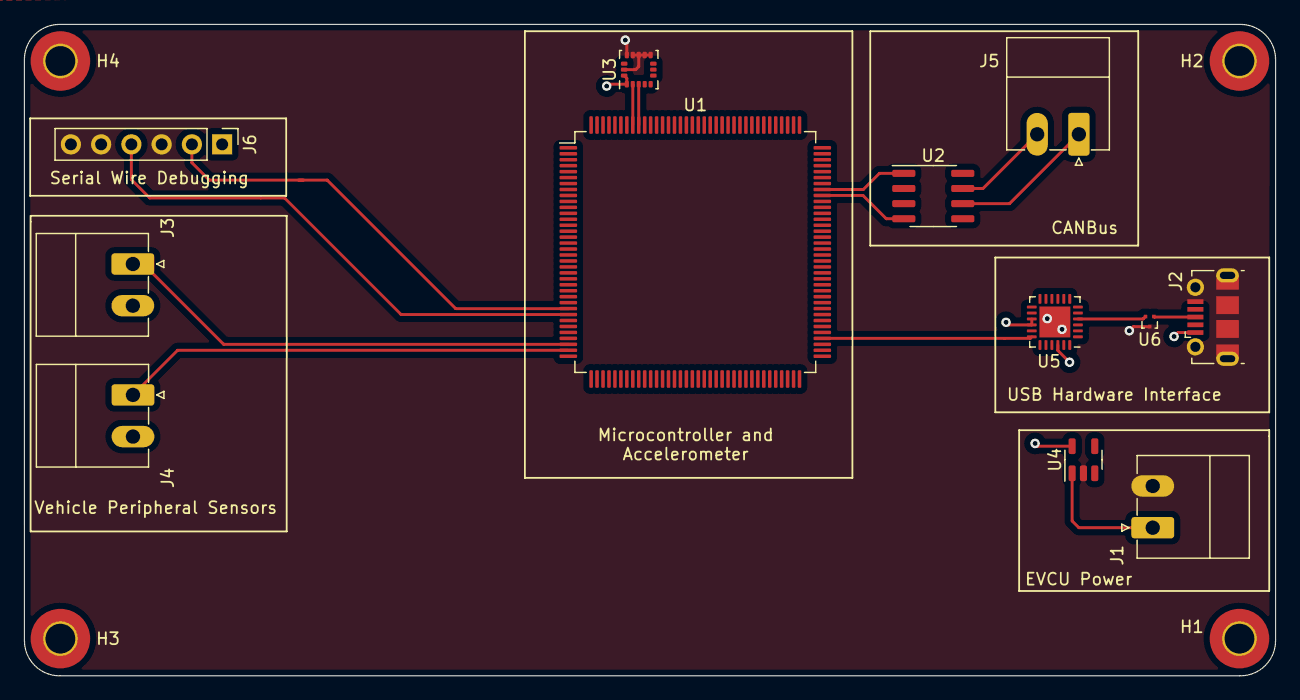
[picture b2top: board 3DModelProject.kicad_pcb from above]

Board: 4 copper layers, 105.1 x 54.7 mm, 16 parts (0 on the bottom side), 16 nets.

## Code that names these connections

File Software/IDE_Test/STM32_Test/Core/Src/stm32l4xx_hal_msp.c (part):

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    __HAL_RCC_GPIOA_CLK_ENABLE();
    __HAL_RCC_GPIOB_CLK_ENABLE();
    /**ADC1 GPIO Configuration
    PC3     ------> ADC1_IN4
    PA0     ------> ADC1_IN5
    PC4     ------> ADC1_IN13
    PA1     ------> ADC1_IN6
    PA7     ------> ADC1_IN12
    PA2     ------> ADC1_IN7
    PB0     ------> ADC1_IN15
    */
    GPIO_InitStruct.Pin = ARD_A2_Pin|ARD_A1_Pin;
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    __HAL_RCC_ADC_CLK_DISABLE();

    /**ADC1 GPIO Configuration
    PC3     ------> ADC1_IN4
    PA0     ------> ADC1_IN5
    PC4     ------> ADC1_IN13
    PA1     ------> ADC1_IN6
    PA7     ------> ADC1_IN12
    PA2     ------> ADC1_IN7
    PB0     ------> ADC1_IN15
    */
    HAL_GPIO_DeInit(GPIOC, ARD_A2_Pin|ARD_A1_Pin);
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
    __HAL_RCC_GPIOA_CLK_ENABLE();
    /**CAN1 GPIO Configuration
    PA12     ------> CAN1_TX
    PA11     ------> CAN1_RX
    */
    GPIO_InitStruct.Pin = GPIO_PIN_12|GPIO_PIN_11;
    GPIO_InitStruct.Mode = GPIO_MODE_AF_PP;
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    __HAL_RCC_CAN1_CLK_DISABLE();

    /**CAN1 GPIO Configuration
    PA12     ------> CAN1_TX
    PA11     ------> CAN1_RX
    */
    HAL_GPIO_DeInit(GPIOA, GPIO_PIN_12|GPIO_PIN_11);

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    __HAL_RCC_GPIOD_CLK_ENABLE();
    __HAL_RCC_GPIOC_CLK_ENABLE();
    /**SDMMC1 GPIO Configuration
    PD2     ------> SDMMC1_CMD
    PC10     ------> SDMMC1_D2
    PC11     ------> SDMMC1_D3
    PC12     ------> SDMMC1_CK
    PC8     ------> SDMMC1_D0
    PC9     ------> SDMMC1_D1
    */
    GPIO_InitStruct.Pin = uSD_CMD_Pin;
    GPIO_InitStruct.Mode = GPIO_MODE_AF_PP;
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    __HAL_RCC_SDMMC1_CLK_DISABLE();

    /**SDMMC1 GPIO Configuration
    PD2     ------> SDMMC1_CMD
    PC10     ------> SDMMC1_D2
    PC11     ------> SDMMC1_D3
    PC12     ------> SDMMC1_CK
    PC8     ------> SDMMC1_D0
    PC9     ------> SDMMC1_D1
    */
    HAL_GPIO_DeInit(uSD_CMD_GPIO_Port, uSD_CMD_Pin);

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
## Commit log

2022-10-27 comm 3d model
2022-10-27 3d model
2022-11-17 zips
2022-11-17 Rev A files
2022-11-17 gitignore
2022-11-17 board
2022-11-17 lol, lmao even
2022-11-17 hahah
2022-11-17 MCU caps
2022-11-17 SWD and 3.3, 5V regs
2022-11-17 some more components
2022-11-18 sd beginning
2022-11-18 please stop with the trello
2022-11-18 schemes
2022-11-18 semes
2022-11-18 scemes
2022-11-18 poeosp
2022-11-18 schematic overview
2022-11-18 inductor rating
2022-11-18 pung
2022-11-18 BOM stuff
2022-11-19 CANBUS esd
2022-11-19 120R resistor for CANH_L
2022-11-19 esd protection
2022-11-20 EVCU BOM
2022-11-20 joe mamama
2022-11-20 WAPWAPWAPWAPWAPWAP
2022-12-09 what
2022-12-22 nom update
2023-01-10 jan 10 buck sd changes
2023-01-16 Added proposal file
2023-01-16 Changed Schematic PDF
2023-01-18 backups
2023-01-18 finishing schematic
2023-01-18 SCHEMATIC finish, connector footprint remaining
2023-01-20 Not done some BSE connections and some footprints
2023-01-20 basically done, start layout
2023-01-20 should be done.
2023-01-20 cap 1206 change, fuse, lin reg to 1117, testpoints, bom additions
2023-01-24 accelerometer layout and op-amp footprint
2023-01-24 software
2023-01-25 dcdc and filter layout
2023-01-25 PCB layout for 1st iteration done, some labelling required
2023-02-03 layout
2023-02-09 ur mom
2023-02-12 silkscreen and drc clean up
2023-02-13 added vref+ caps, fixed f1 via error, fixed gyro footprint, pcb ready for manufacturing
2023-02-13 bom. pcb. exports
    - updated bom added q1, some other capacitors. updated component costs
    - added logo to pcb
    - changed swd pins to female socket
    - exported gerbers
    - filled out digikey order form
    - filled out amazon order form
2023-02-15 pcb and bom
    - moved mcu capacitors to top layer
    - rearranged components to shrink pcb
    - replaced j3 with 1x06 phoenix connector
    - replaced j6 with 1x02 male 2.54 header
2023-02-15 more "final" changes
    - simulated and redid op amp voltage scaling for 0-5V to 0-3.3V sensors
    - decreased size of 3.3V copper pour
    - grounded pcb and db9 mounting holes
    - decreased size of board from 122x86 to 87x80 (in last commit but forgot to mention it)
    - moved swd zener diode to top layer, no more components on bottom layer
    - exported gerbers
2023-02-15 parts order
2023-02-15 cleaning up courtyard spacing
2023-02-16 gerbers again
2023-02-22 software config - first flash
2023-02-22 made 2 layer revision of pcb
2023-02-22 微型 USB 到 USB
2023-02-23 wire
2023-02-26 2l grb
2023-02-26 2 layer gerbers
2023-02-26 gebers
2023-02-26 parts oeder
2023-02-26 stencil added to note
2023-02-28 adc set - not done shutting off peripherials
2023-02-28 removed peri we dont ned
2023-03-01 moving vias from pads
2023-03-01 gerbers
2023-03-02 increasing net clearance, changing trace angles, decreasing trace-to-pad width
2023-03-02 converted 2l to 4l
2023-03-02 .gitignore
2023-03-06 4 layer finished, gnd vias
2023-03-07 fixed some silkscreen shit
2023-03-08 silkscreen
2023-03-08 project initialized - added FATFS - RTOS - initialized 2 threads, 1 mutex, and added 1 adc data collection function
2023-03-08 added CAN as a folder - added adc buffer func
2023-03-09 Define file structures for .c and .h user files
2023-03-09 final PCB submission
2023-03-13 moved ADC Task over and initialized header.h
2023-03-16 added comments
2023-03-16 trying to fix the metadata shit
2023-03-16 removed ide work space
2023-03-16 deleted duplicated library files for some reason.
    added SD_task read/write functions and fixed up ADC_task
2023-03-23 edited adc_task, added controller thread and base functions
2023-03-23 can send and recieve, lot of questions abt how open j1939 works
2023-03-23 edited j1939 include file path
2023-03-24 ioc changes
2023-03-25 working ADC samples
2023-03-25 deleted test
2023-03-25 adc works now, lmao
2023-03-27 adc works, controller.c framework set up ish
2023-03-27 adc works, controller.c framework set up, SD card code not tested until hardware arrives
2023-03-27 sd sample works
2023-03-29 sd updates
2023-03-29 controller logic and some sd card config changes made
2023-03-30 EVCU abstract
2023-04-03 Finalized Budget
2023-04-04 everything works, just dump the can stuff in, change clock config and run this baby
2023-04-05 budget
2023-04-05 changed some settings
2023-04-05 can task
2023-04-05 testing
2023-04-06 ioc changes for the MCU - so changes in clk, pin config...etc
2023-04-06 can bus done
2023-04-06 final integration
2023-04-06 backup error log
2023-04-11 code comments
2023-04-11 removed CAN comments
2023-04-11 removed j1939
2023-04-27 there can be peace with humans and the fish people

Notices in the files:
Software/IDE_Test/STM32_Test/Core/Src/stm32l4xx_hal_msp.c:
Copyright (c) 2023 STMicroelectronics.
All rights reserved.
This software is licensed under terms that can be found in the LICENSE file
